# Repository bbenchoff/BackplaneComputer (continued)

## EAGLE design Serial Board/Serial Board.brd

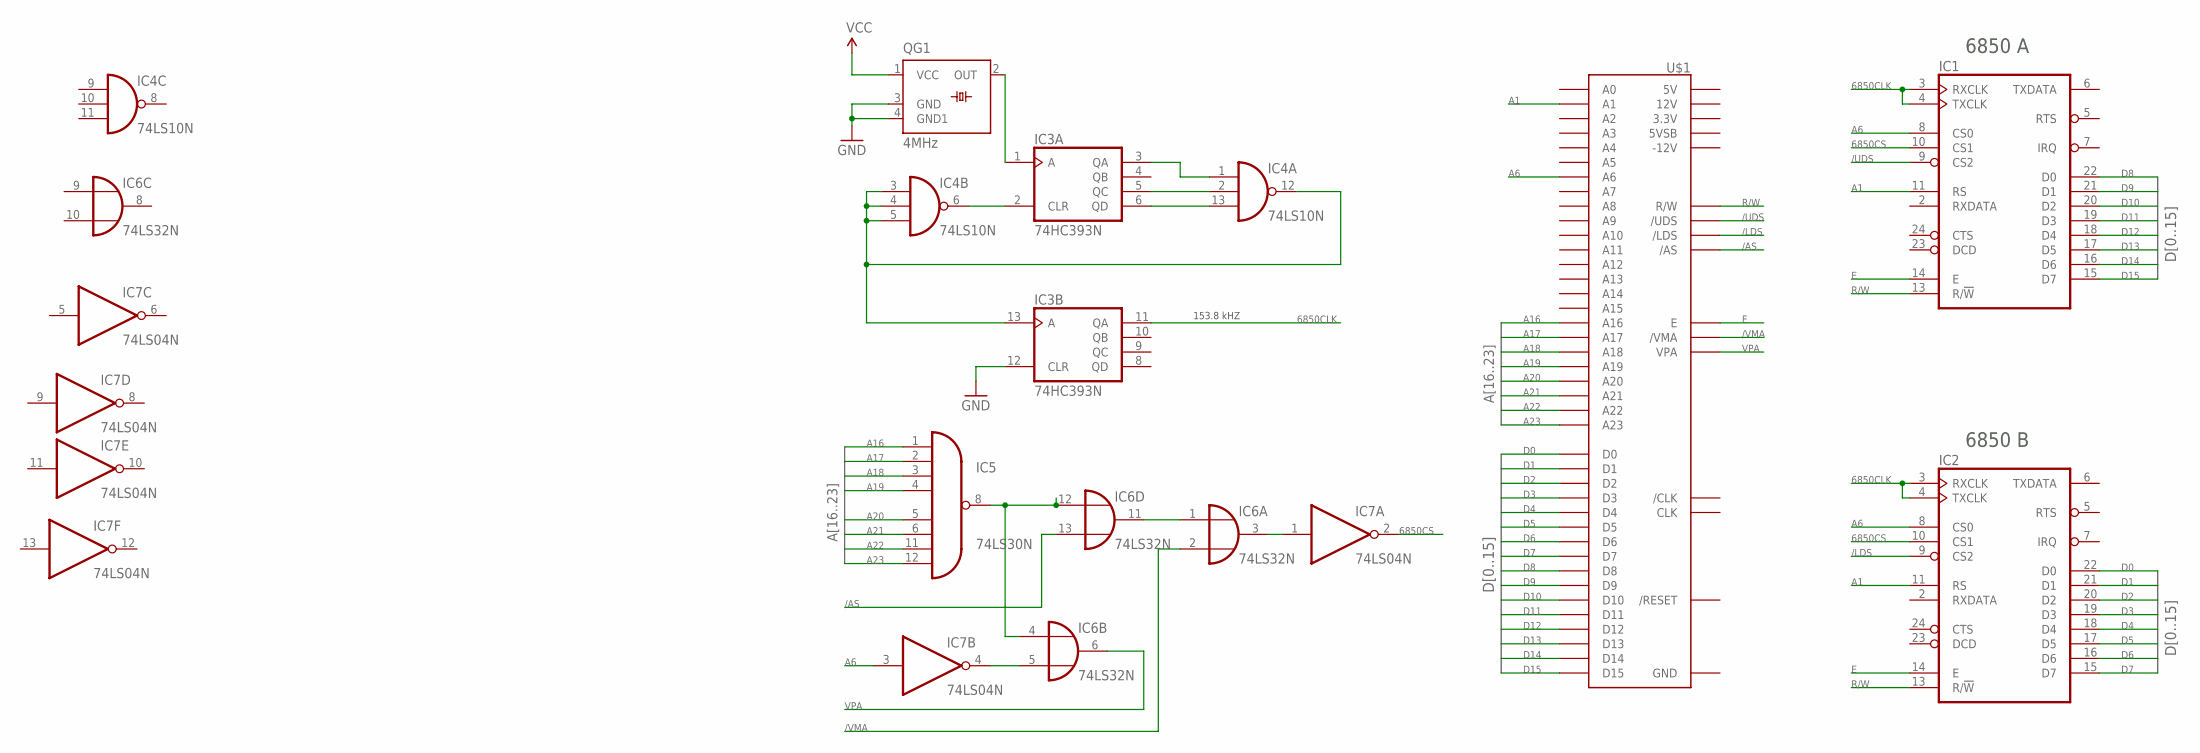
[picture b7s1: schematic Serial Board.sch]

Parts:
IC1, IC2: 6850; DIL24
IC3: 74HC393N; DIL14
IC4: 74LS10N; DIL14
IC5: 74LS30N; DIL14
IC6: 74LS32N; DIL14
IC7: 74LS04N; DIL14
QG1: 4MHz; TC49
U$1: BLANKBOARD

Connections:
6850CLK: IC1.3 (RXCLK), IC1.4 (TXCLK), IC2.3 (RXCLK), IC2.4 (TXCLK), IC3.11 (QA)
6850CS: IC1.10 (CS1), IC2.10 (CS1), IC7.2 (O)
/AS: IC6.13 (I1), U$1./AS
/LDS: IC2.9 (CS2), U$1./LDS
/UDS: IC1.9 (CS2), U$1./UDS
/VMA: IC6.2 (I1), U$1./VMA
A1: IC1.11 (RS), IC2.11 (RS), U$1.A1
A6: IC1.8 (CS0), IC2.8 (CS0), IC7.3 (I), U$1.A6
A16: IC5.1 (I0), U$1.A16
A17: IC5.2 (I1), U$1.A17
A18: IC5.3 (I2), U$1.A18
A19: IC5.4 (I3), U$1.A19
A20: IC5.5 (I4), U$1.A20
A21: IC5.6 (I5), U$1.A21
A22: IC5.11 (I6), U$1.A22
A23: IC5.12 (I7), U$1.A23
D0: IC2.22 (D0), U$1.D0
D1: IC2.21 (D1), U$1.D1
D2: IC2.20 (D2), U$1.D2
D3: IC2.19 (D3), U$1.D3
D4: IC2.18 (D4), U$1.D4
D5: IC2.17 (D5), U$1.D5
D6: IC2.16 (D6), U$1.D6
D7: IC2.15 (D7), U$1.D7
D8: IC1.22 (D0), U$1.D8
D9: IC1.21 (D1), U$1.D9
D10: IC1.20 (D2), U$1.D10
D11: IC1.19 (D3), U$1.D11
D12: IC1.18 (D4), U$1.D12
D13: IC1.17 (D5), U$1.D13
D14: IC1.16 (D6), U$1.D14
D15: IC1.15 (D7), U$1.D15
E: IC1.14 (E), IC2.14 (E), U$1.E
GND: IC3.7 (GND), IC3.12 (CLR), IC4.7 (GND), IC5.7 (GND), IC6.7 (GND), IC7.7 (GND), QG1.3 (GND), QG1.4 (GND1)
unnamed: IC3.5 (QC), IC4.2 (I1)
unnamed: IC3.6 (QD), IC4.13 (I2)
unnamed: IC3.3 (QA), IC4.1 (I0)
unnamed: IC3.2 (CLR), IC4.6 (O)
unnamed: IC3.13 (A), IC4.3 (I0), IC4.4 (I1), IC4.5 (I2), IC4.12 (O)
unnamed: IC5.8 (O), IC6.4 (I0), IC6.12 (I0)
unnamed: IC3.1 (A), QG1.2 (OUT)
unnamed: IC6.5 (I1), IC7.4 (O)
unnamed: IC6.3 (O), IC7.1 (I)
unnamed: IC6.1 (I0), IC6.11 (O)
R/W: IC1.13 (R/!W), IC2.13 (R/!W), U$1.R/W
VCC: IC1.12 (VCC), IC2.12 (VCC), IC3.14 (VCC), IC4.14 (VCC), IC5.14 (VCC), IC6.14 (VCC), IC7.14 (VCC), QG1.1 (VCC)
VPA: IC6.6 (O), U$1.VPA
VSS: IC1.1 (VSS), IC2.1 (VSS)

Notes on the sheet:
6850 A
6850 B
153.8 kHZ

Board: 2 copper layers, 9 parts (0 on the bottom side), 48 nets, no tracks yet.
